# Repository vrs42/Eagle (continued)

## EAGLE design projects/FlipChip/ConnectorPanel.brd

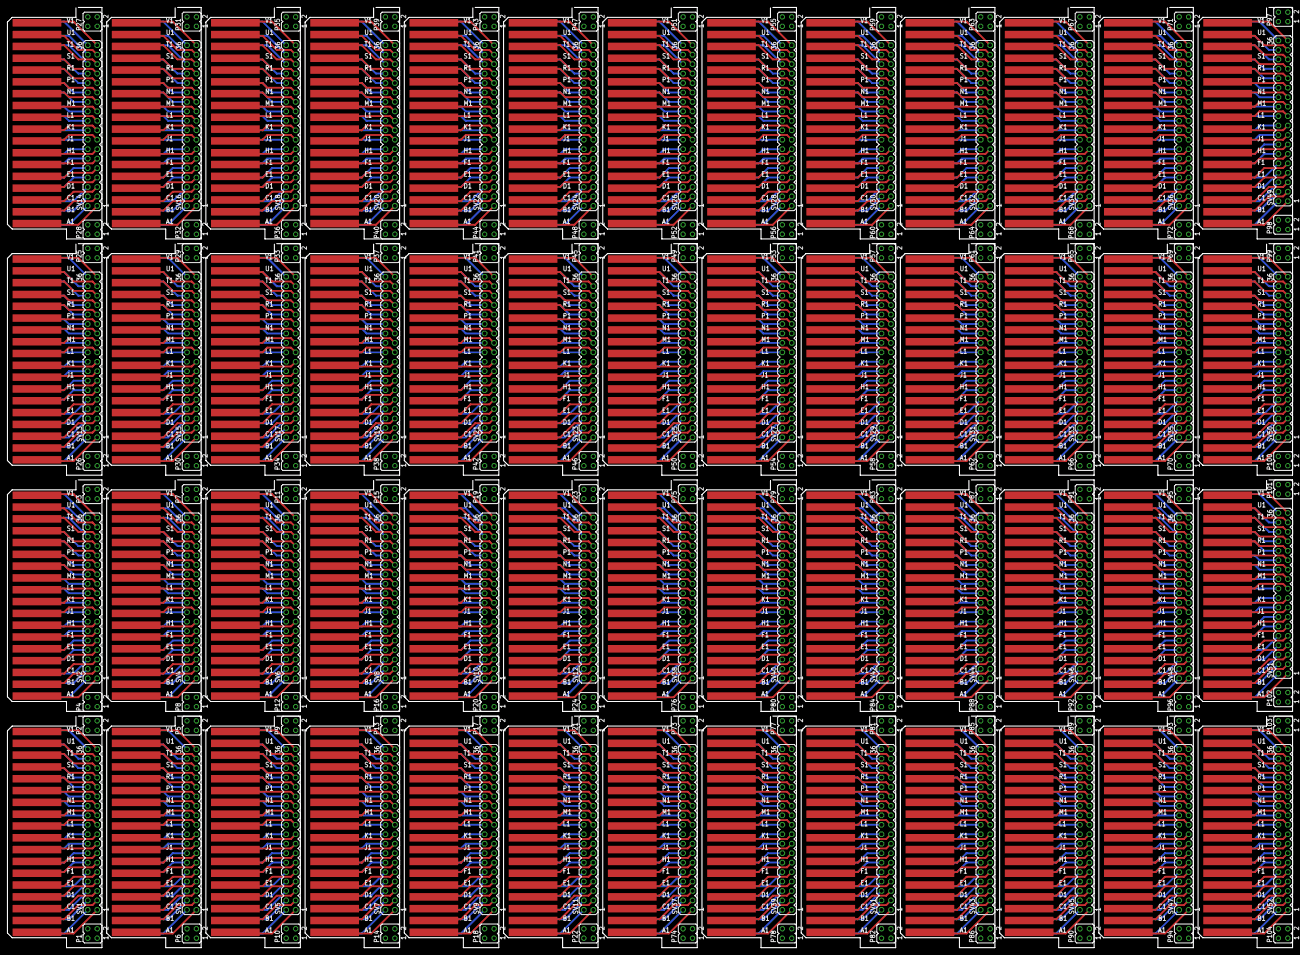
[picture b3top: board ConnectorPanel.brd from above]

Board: 2 copper layers, 345.4 x 252.7 mm, 208 parts (0 on the bottom side), 1872 nets.

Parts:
P1, P2, P3, P4, P5, P6, P7, P8, P9, P10, P11, P12, P13, P14, P15, P16, P17, P18, P19, P20, P21, P22, P23, P24, P25, P26, P27, P28, P29, P30, P31, P32, P33, P34, P35, P36, P37, P38, P39, P40, P41, P42, P43, P44, P45, P46, P47, P48, P49, P50, P51, P52, P53, P54, P55, P56, P57, P58, P59, P60, P61, P62, P63, P64, P65, P66, P67, P68, P69, P70, P71, P72, P73, P74, P75, P76, P77, P78, P79, P80, P81, P82, P83, P84, P85, P86, P87, P88, P89, P90, P91, P92, P93, P94, P95, P96, P97, P98, P99, P100, P101, P102, P103, P104: JP2Q
SV1, SV2, SV3, SV4, SV5, SV6, SV7, SV8, SV9, SV10, SV11, SV12, SV13, SV14, SV15, SV16, SV17, SV18, SV19, SV20, SV21, SV22, SV23, SV24, SV25, SV26, SV27, SV28, SV29, SV30, SV31, SV32, SV33, SV34, SV35, SV36, SV37, SV38, SV39, SV40, SV41, SV42, SV43, SV44, SV45, SV46, SV47, SV48, SV49, SV50, SV51, SV52: MA18-2
U$1, U$2, U$3, U$4, U$5, U$6, U$7, U$8, U$9, U$10, U$11, U$12, U$13, U$14, U$15, U$16, U$17, U$18, U$19, U$20, U$21, U$22, U$23, U$24, U$25, U$26, U$27, U$28, U$29, U$30, U$31, U$32, U$33, U$34, U$35, U$36, U$37, U$38, U$39, U$40, U$41, U$42, U$43, U$44, U$45, U$46, U$47, U$48, U$49, U$50, U$51, U$52: EDGE-CON2

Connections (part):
unnamed: SV1.36, U$1.V2
unnamed: SV1.34, U$1.U2
unnamed: SV1.32, U$1.T2
unnamed: SV1.30, U$1.S2
unnamed: SV1.28, U$1.R2
unnamed: SV1.26, U$1.P2
unnamed: SV1.24, U$1.N2
unnamed: SV1.22, U$1.M2
unnamed: SV1.20, U$1.L2
unnamed: SV1.18, U$1.K2
unnamed: SV1.16, U$1.J2
unnamed: SV1.14, U$1.H2
unnamed: SV1.12, U$1.F2
unnamed: SV1.10, U$1.E2
unnamed: SV1.8, U$1.D2
unnamed: SV1.6, U$1.C2
unnamed: SV1.4, U$1.B2
unnamed: SV1.2, U$1.A2
unnamed: SV1.35, U$1.V1
unnamed: SV1.33, U$1.U1
unnamed: SV1.31, U$1.T1
unnamed: SV1.29, U$1.S1
unnamed: SV1.27, U$1.R1
unnamed: SV1.25, U$1.P1
unnamed: SV1.23, U$1.N1
unnamed: SV1.21, U$1.M1
unnamed: SV1.19, U$1.L1
unnamed: SV1.17, U$1.K1
unnamed: SV1.15, U$1.J1
unnamed: SV1.13, U$1.H1
unnamed: SV1.11, U$1.F1
unnamed: SV1.9, U$1.E1
unnamed: SV1.7, U$1.D1
unnamed: SV1.5, U$1.C1
unnamed: SV1.3, U$1.B1
unnamed: SV1.1, U$1.A1
unnamed: SV2.36, U$2.V2
unnamed: SV2.34, U$2.U2
unnamed: SV2.32, U$2.T2
unnamed: SV2.30, U$2.S2
unnamed: SV2.28, U$2.R2
unnamed: SV2.26, U$2.P2
unnamed: SV2.24, U$2.N2
unnamed: SV2.22, U$2.M2
unnamed: SV2.20, U$2.L2
unnamed: SV2.18, U$2.K2
unnamed: SV2.16, U$2.J2
unnamed: SV2.14, U$2.H2
unnamed: SV2.12, U$2.F2
unnamed: SV2.10, U$2.E2
unnamed: SV2.8, U$2.D2
unnamed: SV2.6, U$2.C2
unnamed: SV2.4, U$2.B2
unnamed: SV2.2, U$2.A2
unnamed: SV2.35, U$2.V1
unnamed: SV2.33, U$2.U1
unnamed: SV2.31, U$2.T1
unnamed: SV2.29, U$2.S1
unnamed: SV2.27, U$2.R1
unnamed: SV2.25, U$2.P1
unnamed: SV2.23, U$2.N1
unnamed: SV2.21, U$2.M1
unnamed: SV2.19, U$2.L1
unnamed: SV2.17, U$2.K1
unnamed: SV2.15, U$2.J1
unnamed: SV2.13, U$2.H1
unnamed: SV2.11, U$2.F1
unnamed: SV2.9, U$2.E1
unnamed: SV2.7, U$2.D1
unnamed: SV2.5, U$2.C1
unnamed: SV2.3, U$2.B1
unnamed: SV2.1, U$2.A1
unnamed: SV3.36, U$3.V2
unnamed: SV3.34, U$3.U2
unnamed: SV3.32, U$3.T2
unnamed: SV3.30, U$3.S2
unnamed: SV3.28, U$3.R2
unnamed: SV3.26, U$3.P2
unnamed: SV3.24, U$3.N2
unnamed: SV3.22, U$3.M2
unnamed: SV3.20, U$3.L2
unnamed: SV3.18, U$3.K2
unnamed: SV3.16, U$3.J2
unnamed: SV3.14, U$3.H2
unnamed: SV3.12, U$3.F2
unnamed: SV3.10, U$3.E2
unnamed: SV3.8, U$3.D2
unnamed: SV3.6, U$3.C2
unnamed: SV3.4, U$3.B2
unnamed: SV3.2, U$3.A2
unnamed: SV3.35, U$3.V1
unnamed: SV3.33, U$3.U1
unnamed: SV3.31, U$3.T1
unnamed: SV3.29, U$3.S1
unnamed: SV3.27, U$3.R1
unnamed: SV3.25, U$3.P1
unnamed: SV3.23, U$3.N1
unnamed: SV3.21, U$3.M1
unnamed: SV3.19, U$3.L1
unnamed: SV3.17, U$3.K1
unnamed: SV3.15, U$3.J1
unnamed: SV3.13, U$3.H1
unnamed: SV3.11, U$3.F1
unnamed: SV3.9, U$3.E1
unnamed: SV3.7, U$3.D1
unnamed: SV3.5, U$3.C1
unnamed: SV3.3, U$3.B1
unnamed: SV3.1, U$3.A1
unnamed: SV4.36, U$4.V2
unnamed: SV4.34, U$4.U2
unnamed: SV4.32, U$4.T2
unnamed: SV4.30, U$4.S2
unnamed: SV4.28, U$4.R2
unnamed: SV4.26, U$4.P2
unnamed: SV4.24, U$4.N2
unnamed: SV4.22, U$4.M2
unnamed: SV4.20, U$4.L2
unnamed: SV4.18, U$4.K2
unnamed: SV4.16, U$4.J2
unnamed: SV4.14, U$4.H2
unnamed: SV4.12, U$4.F2
unnamed: SV4.10, U$4.E2
unnamed: SV4.8, U$4.D2
unnamed: SV4.6, U$4.C2
unnamed: SV4.4, U$4.B2
unnamed: SV4.2, U$4.A2
unnamed: SV4.35, U$4.V1
unnamed: SV4.33, U$4.U1
unnamed: SV4.31, U$4.T1
unnamed: SV4.29, U$4.S1
unnamed: SV4.27, U$4.R1
unnamed: SV4.25, U$4.P1
unnamed: SV4.23, U$4.N1
unnamed: SV4.21, U$4.M1
unnamed: SV4.19, U$4.L1
unnamed: SV4.17, U$4.K1
unnamed: SV4.15, U$4.J1
unnamed: SV4.13, U$4.H1
unnamed: SV4.11, U$4.F1
unnamed: SV4.9, U$4.E1
unnamed: SV4.7, U$4.D1
unnamed: SV4.5, U$4.C1
unnamed: SV4.3, U$4.B1
unnamed: SV4.1, U$4.A1
unnamed: SV5.36, U$5.V2
unnamed: SV5.34, U$5.U2
unnamed: SV5.32, U$5.T2
unnamed: SV5.30, U$5.S2
unnamed: SV5.28, U$5.R2
unnamed: SV5.26, U$5.P2
unnamed: SV5.24, U$5.N2
unnamed: SV5.22, U$5.M2
unnamed: SV5.20, U$5.L2
unnamed: SV5.18, U$5.K2
unnamed: SV5.16, U$5.J2
unnamed: SV5.14, U$5.H2
unnamed: SV5.12, U$5.F2
unnamed: SV5.10, U$5.E2
unnamed: SV5.8, U$5.D2
unnamed: SV5.6, U$5.C2
unnamed: SV5.4, U$5.B2
unnamed: SV5.2, U$5.A2
unnamed: SV5.35, U$5.V1
unnamed: SV5.33, U$5.U1
unnamed: SV5.31, U$5.T1
unnamed: SV5.29, U$5.S1
unnamed: SV5.27, U$5.R1
unnamed: SV5.25, U$5.P1
unnamed: SV5.23, U$5.N1
unnamed: SV5.21, U$5.M1
unnamed: SV5.19, U$5.L1
unnamed: SV5.17, U$5.K1
unnamed: SV5.15, U$5.J1
unnamed: SV5.13, U$5.H1
unnamed: SV5.11, U$5.F1
unnamed: SV5.9, U$5.E1
unnamed: SV5.7, U$5.D1
unnamed: SV5.5, U$5.C1
unnamed: SV5.3, U$5.B1
unnamed: SV5.1, U$5.A1
unnamed: SV6.36, U$6.V2
unnamed: SV6.34, U$6.U2
unnamed: SV6.32, U$6.T2
unnamed: SV6.30, U$6.S2
unnamed: SV6.28, U$6.R2
unnamed: SV6.26, U$6.P2
unnamed: SV6.24, U$6.N2
unnamed: SV6.22, U$6.M2
unnamed: SV6.20, U$6.L2
unnamed: SV6.18, U$6.K2
unnamed: SV6.16, U$6.J2
unnamed: SV6.14, U$6.H2
unnamed: SV6.12, U$6.F2
unnamed: SV6.10, U$6.E2
unnamed: SV6.8, U$6.D2
unnamed: SV6.6, U$6.C2
unnamed: SV6.4, U$6.B2
unnamed: SV6.2, U$6.A2
unnamed: SV6.35, U$6.V1
unnamed: SV6.33, U$6.U1
unnamed: SV6.31, U$6.T1
unnamed: SV6.29, U$6.S1
unnamed: SV6.27, U$6.R1
unnamed: SV6.25, U$6.P1
unnamed: SV6.23, U$6.N1
unnamed: SV6.21, U$6.M1
unnamed: SV6.19, U$6.L1
unnamed: SV6.17, U$6.K1
unnamed: SV6.15, U$6.J1
unnamed: SV6.13, U$6.H1
unnamed: SV6.11, U$6.F1
unnamed: SV6.9, U$6.E1
unnamed: SV6.7, U$6.D1
unnamed: SV6.5, U$6.C1
unnamed: SV6.3, U$6.B1
unnamed: SV6.1, U$6.A1
unnamed: SV7.36, U$7.V2
unnamed: SV7.34, U$7.U2
unnamed: SV7.32, U$7.T2
unnamed: SV7.30, U$7.S2
unnamed: SV7.28, U$7.R2
unnamed: SV7.26, U$7.P2
unnamed: SV7.24, U$7.N2
unnamed: SV7.22, U$7.M2
unnamed: SV7.20, U$7.L2
unnamed: SV7.18, U$7.K2
unnamed: SV7.16, U$7.J2
unnamed: SV7.14, U$7.H2
unnamed: SV7.12, U$7.F2
unnamed: SV7.10, U$7.E2
unnamed: SV7.8, U$7.D2
unnamed: SV7.6, U$7.C2
unnamed: SV7.4, U$7.B2
unnamed: SV7.2, U$7.A2
unnamed: SV7.35, U$7.V1
unnamed: SV7.33, U$7.U1
unnamed: SV7.31, U$7.T1
unnamed: SV7.29, U$7.S1
unnamed: SV7.27, U$7.R1
unnamed: SV7.25, U$7.P1
unnamed: SV7.23, U$7.N1
unnamed: SV7.21, U$7.M1
unnamed: SV7.19, U$7.L1
unnamed: SV7.17, U$7.K1
unnamed: SV7.15, U$7.J1
unnamed: SV7.13, U$7.H1
unnamed: SV7.11, U$7.F1
unnamed: SV7.9, U$7.E1
unnamed: SV7.7, U$7.D1
unnamed: SV7.5, U$7.C1
unnamed: SV7.3, U$7.B1
unnamed: SV7.1, U$7.A1
unnamed: SV8.36, U$8.V2
unnamed: SV8.34, U$8.U2
unnamed: SV8.32, U$8.T2
unnamed: SV8.30, U$8.S2
unnamed: SV8.28, U$8.R2
unnamed: SV8.26, U$8.P2
unnamed: SV8.24, U$8.N2
unnamed: SV8.22, U$8.M2
unnamed: SV8.20, U$8.L2
unnamed: SV8.18, U$8.K2
unnamed: SV8.16, U$8.J2
unnamed: SV8.14, U$8.H2
unnamed: SV8.12, U$8.F2
unnamed: SV8.10, U$8.E2
unnamed: SV8.8, U$8.D2
unnamed: SV8.6, U$8.C2
unnamed: SV8.4, U$8.B2
unnamed: SV8.2, U$8.A2
unnamed: SV8.35, U$8.V1
unnamed: SV8.33, U$8.U1
unnamed: SV8.31, U$8.T1
unnamed: SV8.29, U$8.S1
unnamed: SV8.27, U$8.R1
unnamed: SV8.25, U$8.P1
unnamed: SV8.23, U$8.N1
unnamed: SV8.21, U$8.M1
unnamed: SV8.19, U$8.L1
unnamed: SV8.17, U$8.K1
unnamed: SV8.15, U$8.J1
unnamed: SV8.13, U$8.H1
unnamed: SV8.11, U$8.F1
unnamed: SV8.9, U$8.E1
unnamed: SV8.7, U$8.D1
unnamed: SV8.5, U$8.C1
unnamed: SV8.3, U$8.B1
unnamed: SV8.1, U$8.A1
unnamed: SV9.36, U$9.V2
unnamed: SV9.34, U$9.U2
unnamed: SV9.32, U$9.T2
unnamed: SV9.30, U$9.S2
unnamed: SV9.28, U$9.R2
unnamed: SV9.26, U$9.P2
unnamed: SV9.24, U$9.N2
unnamed: SV9.22, U$9.M2
unnamed: SV9.20, U$9.L2
unnamed: SV9.18, U$9.K2
unnamed: SV9.16, U$9.J2
unnamed: SV9.14, U$9.H2
unnamed: SV9.12, U$9.F2
unnamed: SV9.10, U$9.E2
unnamed: SV9.8, U$9.D2
unnamed: SV9.6, U$9.C2
unnamed: SV9.4, U$9.B2
unnamed: SV9.2, U$9.A2
unnamed: SV9.35, U$9.V1
unnamed: SV9.33, U$9.U1
unnamed: SV9.31, U$9.T1
unnamed: SV9.29, U$9.S1
unnamed: SV9.27, U$9.R1
unnamed: SV9.25, U$9.P1
unnamed: SV9.23, U$9.N1
unnamed: SV9.21, U$9.M1
unnamed: SV9.19, U$9.L1
unnamed: SV9.17, U$9.K1
unnamed: SV9.15, U$9.J1
unnamed: SV9.13, U$9.H1
unnamed: SV9.11, U$9.F1
unnamed: SV9.9, U$9.E1
unnamed: SV9.7, U$9.D1
unnamed: SV9.5, U$9.C1
unnamed: SV9.3, U$9.B1
unnamed: SV9.1, U$9.A1
unnamed: SV10.36, U$10.V2
unnamed: SV10.34, U$10.U2
unnamed: SV10.32, U$10.T2
unnamed: SV10.30, U$10.S2
unnamed: SV10.28, U$10.R2
unnamed: SV10.26, U$10.P2
unnamed: SV10.24, U$10.N2
unnamed: SV10.22, U$10.M2
unnamed: SV10.20, U$10.L2
unnamed: SV10.18, U$10.K2
unnamed: SV10.16, U$10.J2
unnamed: SV10.14, U$10.H2
unnamed: SV10.12, U$10.F2
unnamed: SV10.10, U$10.E2
unnamed: SV10.8, U$10.D2
unnamed: SV10.6, U$10.C2
unnamed: SV10.4, U$10.B2
unnamed: SV10.2, U$10.A2
unnamed: SV10.35, U$10.V1
unnamed: SV10.33, U$10.U1
unnamed: SV10.31, U$10.T1
unnamed: SV10.29, U$10.S1
unnamed: SV10.27, U$10.R1
unnamed: SV10.25, U$10.P1
unnamed: SV10.23, U$10.N1
unnamed: SV10.21, U$10.M1
unnamed: SV10.19, U$10.L1
unnamed: SV10.17, U$10.K1
unnamed: SV10.15, U$10.J1
unnamed: SV10.13, U$10.H1
unnamed: SV10.11, U$10.F1
unnamed: SV10.9, U$10.E1
unnamed: SV10.7, U$10.D1
unnamed: SV10.5, U$10.C1
unnamed: SV10.3, U$10.B1
unnamed: SV10.1, U$10.A1
unnamed: SV11.36, U$11.V2
unnamed: SV11.34, U$11.U2
unnamed: SV11.32, U$11.T2
unnamed: SV11.30, U$11.S2
unnamed: SV11.28, U$11.R2
unnamed: SV11.26, U$11.P2
unnamed: SV11.24, U$11.N2
unnamed: SV11.22, U$11.M2
unnamed: SV11.20, U$11.L2
unnamed: SV11.18, U$11.K2
unnamed: SV11.16, U$11.J2
unnamed: SV11.14, U$11.H2
unnamed: SV11.12, U$11.F2
unnamed: SV11.10, U$11.E2
unnamed: SV11.8, U$11.D2
unnamed: SV11.6, U$11.C2
unnamed: SV11.4, U$11.B2
unnamed: SV11.2, U$11.A2
unnamed: SV11.35, U$11.V1
unnamed: SV11.33, U$11.U1
unnamed: SV11.31, U$11.T1
unnamed: SV11.29, U$11.S1
unnamed: SV11.27, U$11.R1
unnamed: SV11.25, U$11.P1
unnamed: SV11.23, U$11.N1
unnamed: SV11.21, U$11.M1
unnamed: SV11.19, U$11.L1
unnamed: SV11.17, U$11.K1
unnamed: SV11.15, U$11.J1
unnamed: SV11.13, U$11.H1
unnamed: SV11.11, U$11.F1
unnamed: SV11.9, U$11.E1
unnamed: SV11.7, U$11.D1
unnamed: SV11.5, U$11.C1
unnamed: SV11.3, U$11.B1
unnamed: SV11.1, U$11.A1
unnamed: SV12.36, U$12.V2
unnamed: SV12.34, U$12.U2
unnamed: SV12.32, U$12.T2
unnamed: SV12.30, U$12.S2
unnamed: SV12.28, U$12.R2
unnamed: SV12.26, U$12.P2
unnamed: SV12.24, U$12.N2
unnamed: SV12.22, U$12.M2
unnamed: SV12.20, U$12.L2
unnamed: SV12.18, U$12.K2
unnamed: SV12.16, U$12.J2
unnamed: SV12.14, U$12.H2
unnamed: SV12.12, U$12.F2
unnamed: SV12.10, U$12.E2
unnamed: SV12.8, U$12.D2
unnamed: SV12.6, U$12.C2
unnamed: SV12.4, U$12.B2
unnamed: SV12.2, U$12.A2
unnamed: SV12.35, U$12.V1
unnamed: SV12.33, U$12.U1
unnamed: SV12.31, U$12.T1
unnamed: SV12.29, U$12.S1
unnamed: SV12.27, U$12.R1
unnamed: SV12.25, U$12.P1
unnamed: SV12.23, U$12.N1
unnamed: SV12.21, U$12.M1
unnamed: SV12.19, U$12.L1
unnamed: SV12.17, U$12.K1
unnamed: SV12.15, U$12.J1
unnamed: SV12.13, U$12.H1
unnamed: SV12.11, U$12.F1
unnamed: SV12.9, U$12.E1
unnamed: SV12.7, U$12.D1
unnamed: SV12.5, U$12.C1
unnamed: SV12.3, U$12.B1
unnamed: SV12.1, U$12.A1
unnamed: SV13.36, U$13.V2
unnamed: SV13.34, U$13.U2
unnamed: SV13.32, U$13.T2
unnamed: SV13.30, U$13.S2
unnamed: SV13.28, U$13.R2
unnamed: SV13.26, U$13.P2
unnamed: SV13.24, U$13.N2
unnamed: SV13.22, U$13.M2
unnamed: SV13.20, U$13.L2
unnamed: SV13.18, U$13.K2
unnamed: SV13.16, U$13.J2
unnamed: SV13.14, U$13.H2
unnamed: SV13.12, U$13.F2
unnamed: SV13.10, U$13.E2
unnamed: SV13.8, U$13.D2
unnamed: SV13.6, U$13.C2
unnamed: SV13.4, U$13.B2
unnamed: SV13.2, U$13.A2
unnamed: SV13.35, U$13.V1
unnamed: SV13.33, U$13.U1
unnamed: SV13.31, U$13.T1
unnamed: SV13.29, U$13.S1
unnamed: SV13.27, U$13.R1
unnamed: SV13.25, U$13.P1
unnamed: SV13.23, U$13.N1
unnamed: SV13.21, U$13.M1
unnamed: SV13.19, U$13.L1
unnamed: SV13.17, U$13.K1
unnamed: SV13.15, U$13.J1
unnamed: SV13.13, U$13.H1
unnamed: SV13.11, U$13.F1
unnamed: SV13.9, U$13.E1
unnamed: SV13.7, U$13.D1
unnamed: SV13.5, U$13.C1
unnamed: SV13.3, U$13.B1
unnamed: SV13.1, U$13.A1
unnamed: SV14.36, U$14.V2
unnamed: SV14.34, U$14.U2
unnamed: SV14.32, U$14.T2
unnamed: SV14.30, U$14.S2
unnamed: SV14.28, U$14.R2
unnamed: SV14.26, U$14.P2
unnamed: SV14.24, U$14.N2
unnamed: SV14.22, U$14.M2
unnamed: SV14.20, U$14.L2
unnamed: SV14.18, U$14.K2
unnamed: SV14.16, U$14.J2
unnamed: SV14.14, U$14.H2
unnamed: SV14.12, U$14.F2
unnamed: SV14.10, U$14.E2
unnamed: SV14.8, U$14.D2
unnamed: SV14.6, U$14.C2
unnamed: SV14.4, U$14.B2
unnamed: SV14.2, U$14.A2
unnamed: SV14.35, U$14.V1
unnamed: SV14.33, U$14.U1
unnamed: SV14.31, U$14.T1
unnamed: SV14.29, U$14.S1
unnamed: SV14.27, U$14.R1
unnamed: SV14.25, U$14.P1
unnamed: SV14.23, U$14.N1
unnamed: SV14.21, U$14.M1
unnamed: SV14.19, U$14.L1
unnamed: SV14.17, U$14.K1
unnamed: SV14.15, U$14.J1
unnamed: SV14.13, U$14.H1
unnamed: SV14.11, U$14.F1
unnamed: SV14.9, U$14.E1
unnamed: SV14.7, U$14.D1
unnamed: SV14.5, U$14.C1
unnamed: SV14.3, U$14.B1
unnamed: SV14.1, U$14.A1
unnamed: SV15.36, U$15.V2
unnamed: SV15.34, U$15.U2
unnamed: SV15.32, U$15.T2
unnamed: SV15.30, U$15.S2
unnamed: SV15.28, U$15.R2
unnamed: SV15.26, U$15.P2
unnamed: SV15.24, U$15.N2
unnamed: SV15.22, U$15.M2
unnamed: SV15.20, U$15.L2
unnamed: SV15.18, U$15.K2
unnamed: SV15.16, U$15.J2
unnamed: SV15.14, U$15.H2
unnamed: SV15.12, U$15.F2
unnamed: SV15.10, U$15.E2
unnamed: SV15.8, U$15.D2
unnamed: SV15.6, U$15.C2
unnamed: SV15.4, U$15.B2
unnamed: SV15.2, U$15.A2
unnamed: SV15.35, U$15.V1
unnamed: SV15.33, U$15.U1
unnamed: SV15.31, U$15.T1
unnamed: SV15.29, U$15.S1
unnamed: SV15.27, U$15.R1
unnamed: SV15.25, U$15.P1
unnamed: SV15.23, U$15.N1
unnamed: SV15.21, U$15.M1
unnamed: SV15.19, U$15.L1
unnamed: SV15.17, U$15.K1
unnamed: SV15.15, U$15.J1
unnamed: SV15.13, U$15.H1
unnamed: SV15.11, U$15.F1
unnamed: SV15.9, U$15.E1
unnamed: SV15.7, U$15.D1
unnamed: SV15.5, U$15.C1
unnamed: SV15.3, U$15.B1
unnamed: SV15.1, U$15.A1
unnamed: SV16.36, U$16.V2
unnamed: SV16.34, U$16.U2
unnamed: SV16.32, U$16.T2
unnamed: SV16.30, U$16.S2
unnamed: SV16.28, U$16.R2
unnamed: SV16.26, U$16.P2
unnamed: SV16.24, U$16.N2
unnamed: SV16.22, U$16.M2
unnamed: SV16.20, U$16.L2
unnamed: SV16.18, U$16.K2
unnamed: SV16.16, U$16.J2
unnamed: SV16.14, U$16.H2
unnamed: SV16.12, U$16.F2
unnamed: SV16.10, U$16.E2
unnamed: SV16.8, U$16.D2
unnamed: SV16.6, U$16.C2
unnamed: SV16.4, U$16.B2
unnamed: SV16.2, U$16.A2
unnamed: SV16.35, U$16.V1
unnamed: SV16.33, U$16.U1
unnamed: SV16.31, U$16.T1
unnamed: SV16.29, U$16.S1
unnamed: SV16.27, U$16.R1
unnamed: SV16.25, U$16.P1
unnamed: SV16.23, U$16.N1
unnamed: SV16.21, U$16.M1
unnamed: SV16.19, U$16.L1
unnamed: SV16.17, U$16.K1
unnamed: SV16.15, U$16.J1
unnamed: SV16.13, U$16.H1
unnamed: SV16.11, U$16.F1
unnamed: SV16.9, U$16.E1
unnamed: SV16.7, U$16.D1
unnamed: SV16.5, U$16.C1
unnamed: SV16.3, U$16.B1
unnamed: SV16.1, U$16.A1
unnamed: SV17.36, U$17.V2
unnamed: SV17.34, U$17.U2
unnamed: SV17.32, U$17.T2
unnamed: SV17.30, U$17.S2
unnamed: SV17.28, U$17.R2
unnamed: SV17.26, U$17.P2
unnamed: SV17.24, U$17.N2
unnamed: SV17.22, U$17.M2
unnamed: SV17.20, U$17.L2
unnamed: SV17.18, U$17.K2
unnamed: SV17.16, U$17.J2
unnamed: SV17.14, U$17.H2
unnamed: SV17.12, U$17.F2
unnamed: SV17.10, U$17.E2
unnamed: SV17.8, U$17.D2
unnamed: SV17.6, U$17.C2
unnamed: SV17.4, U$17.B2
unnamed: SV17.2, U$17.A2
unnamed: SV17.35, U$17.V1
unnamed: SV17.33, U$17.U1
unnamed: SV17.31, U$17.T1
unnamed: SV17.29, U$17.S1
unnamed: SV17.27, U$17.R1
unnamed: SV17.25, U$17.P1
unnamed: SV17.23, U$17.N1
unnamed: SV17.21, U$17.M1
unnamed: SV17.19, U$17.L1
unnamed: SV17.17, U$17.K1
unnamed: SV17.15, U$17.J1
unnamed: SV17.13, U$17.H1
unnamed: SV17.11, U$17.F1
unnamed: SV17.9, U$17.E1
unnamed: SV17.7, U$17.D1
unnamed: SV17.5, U$17.C1
unnamed: SV17.3, U$17.B1
unnamed: SV17.1, U$17.A1
unnamed: SV18.36, U$18.V2
unnamed: SV18.34, U$18.U2
unnamed: SV18.32, U$18.T2
unnamed: SV18.30, U$18.S2
unnamed: SV18.28, U$18.R2
unnamed: SV18.26, U$18.P2
unnamed: SV18.24, U$18.N2
unnamed: SV18.22, U$18.M2
unnamed: SV18.20, U$18.L2
unnamed: SV18.18, U$18.K2
unnamed: SV18.16, U$18.J2
unnamed: SV18.14, U$18.H2
unnamed: SV18.12, U$18.F2
unnamed: SV18.10, U$18.E2
unnamed: SV18.8, U$18.D2
unnamed: SV18.6, U$18.C2
unnamed: SV18.4, U$18.B2
unnamed: SV18.2, U$18.A2
unnamed: SV18.35, U$18.V1
unnamed: SV18.33, U$18.U1
unnamed: SV18.31, U$18.T1
unnamed: SV18.29, U$18.S1
unnamed: SV18.27, U$18.R1
unnamed: SV18.25, U$18.P1
unnamed: SV18.23, U$18.N1
unnamed: SV18.21, U$18.M1
unnamed: SV18.19, U$18.L1
unnamed: SV18.17, U$18.K1
unnamed: SV18.15, U$18.J1
unnamed: SV18.13, U$18.H1
unnamed: SV18.11, U$18.F1
unnamed: SV18.9, U$18.E1
unnamed: SV18.7, U$18.D1
unnamed: SV18.5, U$18.C1
unnamed: SV18.3, U$18.B1
unnamed: SV18.1, U$18.A1
unnamed: SV19.36, U$19.V2
unnamed: SV19.34, U$19.U2
unnamed: SV19.32, U$19.T2
unnamed: SV19.30, U$19.S2
unnamed: SV19.28, U$19.R2
unnamed: SV19.26, U$19.P2
unnamed: SV19.24, U$19.N2
unnamed: SV19.22, U$19.M2
unnamed: SV19.20, U$19.L2
unnamed: SV19.18, U$19.K2
unnamed: SV19.16, U$19.J2
unnamed: SV19.14, U$19.H2
unnamed: SV19.12, U$19.F2
unnamed: SV19.10, U$19.E2
unnamed: SV19.8, U$19.D2
unnamed: SV19.6, U$19.C2
unnamed: SV19.4, U$19.B2
unnamed: SV19.2, U$19.A2
unnamed: SV19.35, U$19.V1
unnamed: SV19.33, U$19.U1
unnamed: SV19.31, U$19.T1
unnamed: SV19.29, U$19.S1
unnamed: SV19.27, U$19.R1
unnamed: SV19.25, U$19.P1
unnamed: SV19.23, U$19.N1
unnamed: SV19.21, U$19.M1
unnamed: SV19.19, U$19.L1
unnamed: SV19.17, U$19.K1
unnamed: SV19.15, U$19.J1
unnamed: SV19.13, U$19.H1
unnamed: SV19.11, U$19.F1
unnamed: SV19.9, U$19.E1
unnamed: SV19.7, U$19.D1
unnamed: SV19.5, U$19.C1
unnamed: SV19.3, U$19.B1
unnamed: SV19.1, U$19.A1
unnamed: SV20.36, U$20.V2
unnamed: SV20.34, U$20.U2
unnamed: SV20.32, U$20.T2
unnamed: SV20.30, U$20.S2
unnamed: SV20.28, U$20.R2
unnamed: SV20.26, U$20.P2
unnamed: SV20.24, U$20.N2
unnamed: SV20.22, U$20.M2
unnamed: SV20.20, U$20.L2
unnamed: SV20.18, U$20.K2
unnamed: SV20.16, U$20.J2
unnamed: SV20.14, U$20.H2
unnamed: SV20.12, U$20.F2
unnamed: SV20.10, U$20.E2
unnamed: SV20.8, U$20.D2
unnamed: SV20.6, U$20.C2
unnamed: SV20.4, U$20.B2
unnamed: SV20.2, U$20.A2
unnamed: SV20.35, U$20.V1
unnamed: SV20.33, U$20.U1
unnamed: SV20.31, U$20.T1
unnamed: SV20.29, U$20.S1
unnamed: SV20.27, U$20.R1
unnamed: SV20.25, U$20.P1
unnamed: SV20.23, U$20.N1
unnamed: SV20.21, U$20.M1
unnamed: SV20.19, U$20.L1
unnamed: SV20.17, U$20.K1
unnamed: SV20.15, U$20.J1
unnamed: SV20.13, U$20.H1
unnamed: SV20.11, U$20.F1
unnamed: SV20.9, U$20.E1
unnamed: SV20.7, U$20.D1
unnamed: SV20.5, U$20.C1
unnamed: SV20.3, U$20.B1
unnamed: SV20.1, U$20.A1
unnamed: SV21.36, U$21.V2
unnamed: SV21.34, U$21.U2
unnamed: SV21.32, U$21.T2
unnamed: SV21.30, U$21.S2
unnamed: SV21.28, U$21.R2
unnamed: SV21.26, U$21.P2
unnamed: SV21.24, U$21.N2
unnamed: SV21.22, U$21.M2
unnamed: SV21.20, U$21.L2
unnamed: SV21.18, U$21.K2
unnamed: SV21.16, U$21.J2
unnamed: SV21.14, U$21.H2
unnamed: SV21.12, U$21.F2
unnamed: SV21.10, U$21.E2
unnamed: SV21.8, U$21.D2
unnamed: SV21.6, U$21.C2
unnamed: SV21.4, U$21.B2
unnamed: SV21.2, U$21.A2
unnamed: SV21.35, U$21.V1
unnamed: SV21.33, U$21.U1
unnamed: SV21.31, U$21.T1
unnamed: SV21.29, U$21.S1
unnamed: SV21.27, U$21.R1
unnamed: SV21.25, U$21.P1
unnamed: SV21.23, U$21.N1
unnamed: SV21.21, U$21.M1
unnamed: SV21.19, U$21.L1
unnamed: SV21.17, U$21.K1
unnamed: SV21.15, U$21.J1
unnamed: SV21.13, U$21.H1
unnamed: SV21.11, U$21.F1
unnamed: SV21.9, U$21.E1
unnamed: SV21.7, U$21.D1
unnamed: SV21.5, U$21.C1
unnamed: SV21.3, U$21.B1
unnamed: SV21.1, U$21.A1
unnamed: SV22.36, U$22.V2
unnamed: SV22.34, U$22.U2
unnamed: SV22.32, U$22.T2
unnamed: SV22.30, U$22.S2
unnamed: SV22.28, U$22.R2
unnamed: SV22.26, U$22.P2
unnamed: SV22.24, U$22.N2
unnamed: SV22.22, U$22.M2
unnamed: SV22.20, U$22.L2
unnamed: SV22.18, U$22.K2
unnamed: SV22.16, U$22.J2
unnamed: SV22.14, U$22.H2
unnamed: SV22.12, U$22.F2
unnamed: SV22.10, U$22.E2
unnamed: SV22.8, U$22.D2
unnamed: SV22.6, U$22.C2
unnamed: SV22.4, U$22.B2
unnamed: SV22.2, U$22.A2
unnamed: SV22.35, U$22.V1
unnamed: SV22.33, U$22.U1
unnamed: SV22.31, U$22.T1
unnamed: SV22.29, U$22.S1
unnamed: SV22.27, U$22.R1
unnamed: SV22.25, U$22.P1
unnamed: SV22.23, U$22.N1
unnamed: SV22.21, U$22.M1
unnamed: SV22.19, U$22.L1
unnamed: SV22.17, U$22.K1
unnamed: SV22.15, U$22.J1
unnamed: SV22.13, U$22.H1
unnamed: SV22.11, U$22.F1
unnamed: SV22.9, U$22.E1
unnamed: SV22.7, U$22.D1
unnamed: SV22.5, U$22.C1
unnamed: SV22.3, U$22.B1
unnamed: SV22.1, U$22.A1
unnamed: SV23.36, U$23.V2
unnamed: SV23.34, U$23.U2
unnamed: SV23.32, U$23.T2
unnamed: SV23.30, U$23.S2
unnamed: SV23.28, U$23.R2
unnamed: SV23.26, U$23.P2
unnamed: SV23.24, U$23.N2
unnamed: SV23.22, U$23.M2
unnamed: SV23.20, U$23.L2
unnamed: SV23.18, U$23.K2
unnamed: SV23.16, U$23.J2
unnamed: SV23.14, U$23.H2
unnamed: SV23.12, U$23.F2
unnamed: SV23.10, U$23.E2
unnamed: SV23.8, U$23.D2
unnamed: SV23.6, U$23.C2
unnamed: SV23.4, U$23.B2
unnamed: SV23.2, U$23.A2
unnamed: SV23.35, U$23.V1
unnamed: SV23.33, U$23.U1
unnamed: SV23.31, U$23.T1
unnamed: SV23.29, U$23.S1
unnamed: SV23.27, U$23.R1
unnamed: SV23.25, U$23.P1
unnamed: SV23.23, U$23.N1
unnamed: SV23.21, U$23.M1
unnamed: SV23.19, U$23.L1
unnamed: SV23.17, U$23.K1
unnamed: SV23.15, U$23.J1
unnamed: SV23.13, U$23.H1
unnamed: SV23.11, U$23.F1
unnamed: SV23.9, U$23.E1
unnamed: SV23.7, U$23.D1
unnamed: SV23.5, U$23.C1
unnamed: SV23.3, U$23.B1
unnamed: SV23.1, U$23.A1
unnamed: SV24.36, U$24.V2
unnamed: SV24.34, U$24.U2
unnamed: SV24.32, U$24.T2
unnamed: SV24.30, U$24.S2
unnamed: SV24.28, U$24.R2
unnamed: SV24.26, U$24.P2
unnamed: SV24.24, U$24.N2
unnamed: SV24.22, U$24.M2
unnamed: SV24.20, U$24.L2
unnamed: SV24.18, U$24.K2
unnamed: SV24.16, U$24.J2
unnamed: SV24.14, U$24.H2
unnamed: SV24.12, U$24.F2
unnamed: SV24.10, U$24.E2
unnamed: SV24.8, U$24.D2
unnamed: SV24.6, U$24.C2
unnamed: SV24.4, U$24.B2
unnamed: SV24.2, U$24.A2
unnamed: SV24.35, U$24.V1
unnamed: SV24.33, U$24.U1
unnamed: SV24.31, U$24.T1
unnamed: SV24.29, U$24.S1
unnamed: SV24.27, U$24.R1
unnamed: SV24.25, U$24.P1
unnamed: SV24.23, U$24.N1
unnamed: SV24.21, U$24.M1
unnamed: SV24.19, U$24.L1
unnamed: SV24.17, U$24.K1
unnamed: SV24.15, U$24.J1
unnamed: SV24.13, U$24.H1
unnamed: SV24.11, U$24.F1
unnamed: SV24.9, U$24.E1
unnamed: SV24.7, U$24.D1
unnamed: SV24.5, U$24.C1
unnamed: SV24.3, U$24.B1
unnamed: SV24.1, U$24.A1
unnamed: SV25.36, U$25.V2
unnamed: SV25.34, U$25.U2
unnamed: SV25.32, U$25.T2
unnamed: SV25.30, U$25.S2
unnamed: SV25.28, U$25.R2
unnamed: SV25.26, U$25.P2
unnamed: SV25.24, U$25.N2
unnamed: SV25.22, U$25.M2
unnamed: SV25.20, U$25.L2
unnamed: SV25.18, U$25.K2
unnamed: SV25.16, U$25.J2
unnamed: SV25.14, U$25.H2
unnamed: SV25.12, U$25.F2
unnamed: SV25.10, U$25.E2
unnamed: SV25.8, U$25.D2
unnamed: SV25.6, U$25.C2
unnamed: SV25.4, U$25.B2
unnamed: SV25.2, U$25.A2
unnamed: SV25.35, U$25.V1
unnamed: SV25.33, U$25.U1
unnamed: SV25.31, U$25.T1
unnamed: SV25.29, U$25.S1
unnamed: SV25.27, U$25.R1
unnamed: SV25.25, U$25.P1
unnamed: SV25.23, U$25.N1
unnamed: SV25.21, U$25.M1
unnamed: SV25.19, U$25.L1
unnamed: SV25.17, U$25.K1
unnamed: SV25.15, U$25.J1
unnamed: SV25.13, U$25.H1
unnamed: SV25.11, U$25.F1
unnamed: SV25.9, U$25.E1
unnamed: SV25.7, U$25.D1
unnamed: SV25.5, U$25.C1
unnamed: SV25.3, U$25.B1
unnamed: SV25.1, U$25.A1
unnamed: SV26.36, U$26.V2
unnamed: SV26.34, U$26.U2
unnamed: SV26.32, U$26.T2
unnamed: SV26.30, U$26.S2
unnamed: SV26.28, U$26.R2
unnamed: SV26.26, U$26.P2
unnamed: SV26.24, U$26.N2
unnamed: SV26.22, U$26.M2
unnamed: SV26.20, U$26.L2
unnamed: SV26.18, U$26.K2
unnamed: SV26.16, U$26.J2
unnamed: SV26.14, U$26.H2
unnamed: SV26.12, U$26.F2
unnamed: SV26.10, U$26.E2
unnamed: SV26.8, U$26.D2
unnamed: SV26.6, U$26.C2
unnamed: SV26.4, U$26.B2
unnamed: SV26.2, U$26.A2
unnamed: SV26.35, U$26.V1
unnamed: SV26.33, U$26.U1
unnamed: SV26.31, U$26.T1
unnamed: SV26.29, U$26.S1
unnamed: SV26.27, U$26.R1
unnamed: SV26.25, U$26.P1
unnamed: SV26.23, U$26.N1
unnamed: SV26.21, U$26.M1
unnamed: SV26.19, U$26.L1
unnamed: SV26.17, U$26.K1
unnamed: SV26.15, U$26.J1
unnamed: SV26.13, U$26.H1
unnamed: SV26.11, U$26.F1
unnamed: SV26.9, U$26.E1
unnamed: SV26.7, U$26.D1
unnamed: SV26.5, U$26.C1
unnamed: SV26.3, U$26.B1
unnamed: SV26.1, U$26.A1
unnamed: SV27.36, U$27.V2
unnamed: SV27.34, U$27.U2
unnamed: SV27.32, U$27.T2
unnamed: SV27.30, U$27.S2
unnamed: SV27.28, U$27.R2
unnamed: SV27.26, U$27.P2
unnamed: SV27.24, U$27.N2
unnamed: SV27.22, U$27.M2
unnamed: SV27.20, U$27.L2
unnamed: SV27.18, U$27.K2
unnamed: SV27.16, U$27.J2
unnamed: SV27.14, U$27.H2
unnamed: SV27.12, U$27.F2
unnamed: SV27.10, U$27.E2
unnamed: SV27.8, U$27.D2
unnamed: SV27.6, U$27.C2
unnamed: SV27.4, U$27.B2
unnamed: SV27.2, U$27.A2
unnamed: SV27.35, U$27.V1
unnamed: SV27.33, U$27.U1
unnamed: SV27.31, U$27.T1
unnamed: SV27.29, U$27.S1
unnamed: SV27.27, U$27.R1
unnamed: SV27.25, U$27.P1
unnamed: SV27.23, U$27.N1
unnamed: SV27.21, U$27.M1
unnamed: SV27.19, U$27.L1
unnamed: SV27.17, U$27.K1
unnamed: SV27.15, U$27.J1
unnamed: SV27.13, U$27.H1
unnamed: SV27.11, U$27.F1
unnamed: SV27.9, U$27.E1
unnamed: SV27.7, U$27.D1
unnamed: SV27.5, U$27.C1
unnamed: SV27.3, U$27.B1
unnamed: SV27.1, U$27.A1
unnamed: SV28.36, U$28.V2
unnamed: SV28.34, U$28.U2
unnamed: SV28.32, U$28.T2
unnamed: SV28.30, U$28.S2
unnamed: SV28.28, U$28.R2
unnamed: SV28.26, U$28.P2
unnamed: SV28.24, U$28.N2
unnamed: SV28.22, U$28.M2
unnamed: SV28.20, U$28.L2
unnamed: SV28.18, U$28.K2
unnamed: SV28.16, U$28.J2
unnamed: SV28.14, U$28.H2
unnamed: SV28.12, U$28.F2
unnamed: SV28.10, U$28.E2
unnamed: SV28.8, U$28.D2
unnamed: SV28.6, U$28.C2
unnamed: SV28.4, U$28.B2
unnamed: SV28.2, U$28.A2
unnamed: SV28.35, U$28.V1
unnamed: SV28.33, U$28.U1
unnamed: SV28.31, U$28.T1
unnamed: SV28.29, U$28.S1
unnamed: SV28.27, U$28.R1
unnamed: SV28.25, U$28.P1
unnamed: SV28.23, U$28.N1
unnamed: SV28.21, U$28.M1
unnamed: SV28.19, U$28.L1
unnamed: SV28.17, U$28.K1
unnamed: SV28.15, U$28.J1
unnamed: SV28.13, U$28.H1
unnamed: SV28.11, U$28.F1
unnamed: SV28.9, U$28.E1
unnamed: SV28.7, U$28.D1
unnamed: SV28.5, U$28.C1
unnamed: SV28.3, U$28.B1
unnamed: SV28.1, U$28.A1
unnamed: SV29.36, U$29.V2
unnamed: SV29.34, U$29.U2
unnamed: SV29.32, U$29.T2
unnamed: SV29.30, U$29.S2
unnamed: SV29.28, U$29.R2
unnamed: SV29.26, U$29.P2
unnamed: SV29.24, U$29.N2
unnamed: SV29.22, U$29.M2
unnamed: SV29.20, U$29.L2
unnamed: SV29.18, U$29.K2
unnamed: SV29.16, U$29.J2
unnamed: SV29.14, U$29.H2
unnamed: SV29.12, U$29.F2
unnamed: SV29.10, U$29.E2
unnamed: SV29.8, U$29.D2
unnamed: SV29.6, U$29.C2
unnamed: SV29.4, U$29.B2
unnamed: SV29.2, U$29.A2
unnamed: SV29.35, U$29.V1
unnamed: SV29.33, U$29.U1
unnamed: SV29.31, U$29.T1
unnamed: SV29.29, U$29.S1
unnamed: SV29.27, U$29.R1
unnamed: SV29.25, U$29.P1
unnamed: SV29.23, U$29.N1
unnamed: SV29.21, U$29.M1
unnamed: SV29.19, U$29.L1
unnamed: SV29.17, U$29.K1
unnamed: SV29.15, U$29.J1
unnamed: SV29.13, U$29.H1
unnamed: SV29.11, U$29.F1
unnamed: SV29.9, U$29.E1
unnamed: SV29.7, U$29.D1
unnamed: SV29.5, U$29.C1
unnamed: SV29.3, U$29.B1
unnamed: SV29.1, U$29.A1
unnamed: SV30.36, U$30.V2
unnamed: SV30.34, U$30.U2
unnamed: SV30.32, U$30.T2
unnamed: SV30.30, U$30.S2
unnamed: SV30.28, U$30.R2
unnamed: SV30.26, U$30.P2
unnamed: SV30.24, U$30.N2
unnamed: SV30.22, U$30.M2
unnamed: SV30.20, U$30.L2
unnamed: SV30.18, U$30.K2
unnamed: SV30.16, U$30.J2
unnamed: SV30.14, U$30.H2
unnamed: SV30.12, U$30.F2
unnamed: SV30.10, U$30.E2
unnamed: SV30.8, U$30.D2
unnamed: SV30.6, U$30.C2
unnamed: SV30.4, U$30.B2
unnamed: SV30.2, U$30.A2
unnamed: SV30.35, U$30.V1
unnamed: SV30.33, U$30.U1
unnamed: SV30.31, U$30.T1
unnamed: SV30.29, U$30.S1
unnamed: SV30.27, U$30.R1
unnamed: SV30.25, U$30.P1
unnamed: SV30.23, U$30.N1
unnamed: SV30.21, U$30.M1
unnamed: SV30.19, U$30.L1
unnamed: SV30.17, U$30.K1
unnamed: SV30.15, U$30.J1
unnamed: SV30.13, U$30.H1
unnamed: SV30.11, U$30.F1
unnamed: SV30.9, U$30.E1
unnamed: SV30.7, U$30.D1
unnamed: SV30.5, U$30.C1
unnamed: SV30.3, U$30.B1
unnamed: SV30.1, U$30.A1
unnamed: SV31.36, U$31.V2
unnamed: SV31.34, U$31.U2
unnamed: SV31.32, U$31.T2
unnamed: SV31.30, U$31.S2
unnamed: SV31.28, U$31.R2
unnamed: SV31.26, U$31.P2
unnamed: SV31.24, U$31.N2
unnamed: SV31.22, U$31.M2
unnamed: SV31.20, U$31.L2
unnamed: SV31.18, U$31.K2
unnamed: SV31.16, U$31.J2
unnamed: SV31.14, U$31.H2
unnamed: SV31.12, U$31.F2
unnamed: SV31.10, U$31.E2
unnamed: SV31.8, U$31.D2
unnamed: SV31.6, U$31.C2
unnamed: SV31.4, U$31.B2
unnamed: SV31.2, U$31.A2
unnamed: SV31.35, U$31.V1
unnamed: SV31.33, U$31.U1
unnamed: SV31.31, U$31.T1
unnamed: SV31.29, U$31.S1
unnamed: SV31.27, U$31.R1
unnamed: SV31.25, U$31.P1
unnamed: SV31.23, U$31.N1
unnamed: SV31.21, U$31.M1
unnamed: SV31.19, U$31.L1
unnamed: SV31.17, U$31.K1
unnamed: SV31.15, U$31.J1
unnamed: SV31.13, U$31.H1
unnamed: SV31.11, U$31.F1
unnamed: SV31.9, U$31.E1
unnamed: SV31.7, U$31.D1
unnamed: SV31.5, U$31.C1
unnamed: SV31.3, U$31.B1
unnamed: SV31.1, U$31.A1
unnamed: SV32.36, U$32.V2
unnamed: SV32.34, U$32.U2
unnamed: SV32.32, U$32.T2
unnamed: SV32.30, U$32.S2
unnamed: SV32.28, U$32.R2
unnamed: SV32.26, U$32.P2
unnamed: SV32.24, U$32.N2
unnamed: SV32.22, U$32.M2
unnamed: SV32.20, U$32.L2
unnamed: SV32.18, U$32.K2
unnamed: SV32.16, U$32.J2
unnamed: SV32.14, U$32.H2
unnamed: SV32.12, U$32.F2
unnamed: SV32.10, U$32.E2
unnamed: SV32.8, U$32.D2
unnamed: SV32.6, U$32.C2
unnamed: SV32.4, U$32.B2
unnamed: SV32.2, U$32.A2
unnamed: SV32.35, U$32.V1
unnamed: SV32.33, U$32.U1
unnamed: SV32.31, U$32.T1
unnamed: SV32.29, U$32.S1
unnamed: SV32.27, U$32.R1
unnamed: SV32.25, U$32.P1
unnamed: SV32.23, U$32.N1
unnamed: SV32.21, U$32.M1
unnamed: SV32.19, U$32.L1
unnamed: SV32.17, U$32.K1
unnamed: SV32.15, U$32.J1
unnamed: SV32.13, U$32.H1
unnamed: SV32.11, U$32.F1
unnamed: SV32.9, U$32.E1
unnamed: SV32.7, U$32.D1
unnamed: SV32.5, U$32.C1
unnamed: SV32.3, U$32.B1
unnamed: SV32.1, U$32.A1
unnamed: SV33.36, U$33.V2
unnamed: SV33.34, U$33.U2
unnamed: SV33.32, U$33.T2
unnamed: SV33.30, U$33.S2
unnamed: SV33.28, U$33.R2
unnamed: SV33.26, U$33.P2
unnamed: SV33.24, U$33.N2
unnamed: SV33.22, U$33.M2
unnamed: SV33.20, U$33.L2
unnamed: SV33.18, U$33.K2
unnamed: SV33.16, U$33.J2
unnamed: SV33.14, U$33.H2
unnamed: SV33.12, U$33.F2
unnamed: SV33.10, U$33.E2
unnamed: SV33.8, U$33.D2
unnamed: SV33.6, U$33.C2
unnamed: SV33.4, U$33.B2
unnamed: SV33.2, U$33.A2
unnamed: SV33.35, U$33.V1
unnamed: SV33.33, U$33.U1
unnamed: SV33.31, U$33.T1
unnamed: SV33.29, U$33.S1
unnamed: SV33.27, U$33.R1
unnamed: SV33.25, U$33.P1
unnamed: SV33.23, U$33.N1
unnamed: SV33.21, U$33.M1
unnamed: SV33.19, U$33.L1
unnamed: SV33.17, U$33.K1
unnamed: SV33.15, U$33.J1
unnamed: SV33.13, U$33.H1
unnamed: SV33.11, U$33.F1
unnamed: SV33.9, U$33.E1
unnamed: SV33.7, U$33.D1
unnamed: SV33.5, U$33.C1
unnamed: SV33.3, U$33.B1
unnamed: SV33.1, U$33.A1
unnamed: SV34.36, U$34.V2
unnamed: SV34.34, U$34.U2
unnamed: SV34.32, U$34.T2
unnamed: SV34.30, U$34.S2
unnamed: SV34.28, U$34.R2
unnamed: SV34.26, U$34.P2
unnamed: SV34.24, U$34.N2
unnamed: SV34.22, U$34.M2
unnamed: SV34.20, U$34.L2
unnamed: SV34.18, U$34.K2
unnamed: SV34.16, U$34.J2
unnamed: SV34.14, U$34.H2
unnamed: SV34.12, U$34.F2
unnamed: SV34.10, U$34.E2
unnamed: SV34.8, U$34.D2
unnamed: SV34.6, U$34.C2
unnamed: SV34.4, U$34.B2
unnamed: SV34.2, U$34.A2
unnamed: SV34.35, U$34.V1
unnamed: SV34.33, U$34.U1
unnamed: SV34.31, U$34.T1
unnamed: SV34.29, U$34.S1
unnamed: SV34.27, U$34.R1
unnamed: SV34.25, U$34.P1
unnamed: SV34.23, U$34.N1
unnamed: SV34.21, U$34.M1
unnamed: SV34.19, U$34.L1
unnamed: SV34.17, U$34.K1
unnamed: SV34.15, U$34.J1
unnamed: SV34.13, U$34.H1
unnamed: SV34.11, U$34.F1
unnamed: SV34.9, U$34.E1
unnamed: SV34.7, U$34.D1
unnamed: SV34.5, U$34.C1
unnamed: SV34.3, U$34.B1
unnamed: SV34.1, U$34.A1
unnamed: SV35.36, U$35.V2
unnamed: SV35.34, U$35.U2
unnamed: SV35.32, U$35.T2
unnamed: SV35.30, U$35.S2
unnamed: SV35.28, U$35.R2
unnamed: SV35.26, U$35.P2
unnamed: SV35.24, U$35.N2
unnamed: SV35.22, U$35.M2
unnamed: SV35.20, U$35.L2
unnamed: SV35.18, U$35.K2
unnamed: SV35.16, U$35.J2
unnamed: SV35.14, U$35.H2
unnamed: SV35.12, U$35.F2
unnamed: SV35.10, U$35.E2
unnamed: SV35.8, U$35.D2
unnamed: SV35.6, U$35.C2
unnamed: SV35.4, U$35.B2
unnamed: SV35.2, U$35.A2
unnamed: SV35.35, U$35.V1
unnamed: SV35.33, U$35.U1
unnamed: SV35.31, U$35.T1
unnamed: SV35.29, U$35.S1
unnamed: SV35.27, U$35.R1
unnamed: SV35.25, U$35.P1
unnamed: SV35.23, U$35.N1
unnamed: SV35.21, U$35.M1
unnamed: SV35.19, U$35.L1
unnamed: SV35.17, U$35.K1
unnamed: SV35.15, U$35.J1
unnamed: SV35.13, U$35.H1
unnamed: SV35.11, U$35.F1
unnamed: SV35.9, U$35.E1
unnamed: SV35.7, U$35.D1
unnamed: SV35.5, U$35.C1
unnamed: SV35.3, U$35.B1
unnamed: SV35.1, U$35.A1
unnamed: SV36.36, U$36.V2
unnamed: SV36.34, U$36.U2
unnamed: SV36.32, U$36.T2
unnamed: SV36.30, U$36.S2
unnamed: SV36.28, U$36.R2
unnamed: SV36.26, U$36.P2
unnamed: SV36.24, U$36.N2
unnamed: SV36.22, U$36.M2
unnamed: SV36.20, U$36.L2
unnamed: SV36.18, U$36.K2
unnamed: SV36.16, U$36.J2
unnamed: SV36.14, U$36.H2
unnamed: SV36.12, U$36.F2
unnamed: SV36.10, U$36.E2
unnamed: SV36.8, U$36.D2
unnamed: SV36.6, U$36.C2
unnamed: SV36.4, U$36.B2
unnamed: SV36.2, U$36.A2
unnamed: SV36.35, U$36.V1
unnamed: SV36.33, U$36.U1
unnamed: SV36.31, U$36.T1
unnamed: SV36.29, U$36.S1
unnamed: SV36.27, U$36.R1
unnamed: SV36.25, U$36.P1
unnamed: SV36.23, U$36.N1
unnamed: SV36.21, U$36.M1
unnamed: SV36.19, U$36.L1
unnamed: SV36.17, U$36.K1
unnamed: SV36.15, U$36.J1
unnamed: SV36.13, U$36.H1
unnamed: SV36.11, U$36.F1
unnamed: SV36.9, U$36.E1
unnamed: SV36.7, U$36.D1
unnamed: SV36.5, U$36.C1
unnamed: SV36.3, U$36.B1
unnamed: SV36.1, U$36.A1
unnamed: SV37.36, U$37.V2
unnamed: SV37.34, U$37.U2
unnamed: SV37.32, U$37.T2
unnamed: SV37.30, U$37.S2
unnamed: SV37.28, U$37.R2
unnamed: SV37.26, U$37.P2
unnamed: SV37.24, U$37.N2
unnamed: SV37.22, U$37.M2
unnamed: SV37.20, U$37.L2
unnamed: SV37.18, U$37.K2
unnamed: SV37.16, U$37.J2
unnamed: SV37.14, U$37.H2
unnamed: SV37.12, U$37.F2
unnamed: SV37.10, U$37.E2
unnamed: SV37.8, U$37.D2
unnamed: SV37.6, U$37.C2
unnamed: SV37.4, U$37.B2
unnamed: SV37.2, U$37.A2
unnamed: SV37.35, U$37.V1
unnamed: SV37.33, U$37.U1
unnamed: SV37.31, U$37.T1
unnamed: SV37.29, U$37.S1
unnamed: SV37.27, U$37.R1
unnamed: SV37.25, U$37.P1
unnamed: SV37.23, U$37.N1
unnamed: SV37.21, U$37.M1
unnamed: SV37.19, U$37.L1
unnamed: SV37.17, U$37.K1
unnamed: SV37.15, U$37.J1
unnamed: SV37.13, U$37.H1
unnamed: SV37.11, U$37.F1
unnamed: SV37.9, U$37.E1
unnamed: SV37.7, U$37.D1
unnamed: SV37.5, U$37.C1
unnamed: SV37.3, U$37.B1
unnamed: SV37.1, U$37.A1
unnamed: SV38.36, U$38.V2
unnamed: SV38.34, U$38.U2
unnamed: SV38.32, U$38.T2
unnamed: SV38.30, U$38.S2
unnamed: SV38.28, U$38.R2
unnamed: SV38.26, U$38.P2
unnamed: SV38.24, U$38.N2
unnamed: SV38.22, U$38.M2
unnamed: SV38.20, U$38.L2
unnamed: SV38.18, U$38.K2
unnamed: SV38.16, U$38.J2
unnamed: SV38.14, U$38.H2
unnamed: SV38.12, U$38.F2
unnamed: SV38.10, U$38.E2
unnamed: SV38.8, U$38.D2
unnamed: SV38.6, U$38.C2
unnamed: SV38.4, U$38.B2
unnamed: SV38.2, U$38.A2
unnamed: SV38.35, U$38.V1
unnamed: SV38.33, U$38.U1
unnamed: SV38.31, U$38.T1
unnamed: SV38.29, U$38.S1
unnamed: SV38.27, U$38.R1
unnamed: SV38.25, U$38.P1
unnamed: SV38.23, U$38.N1
unnamed: SV38.21, U$38.M1
unnamed: SV38.19, U$38.L1
unnamed: SV38.17, U$38.K1
unnamed: SV38.15, U$38.J1
unnamed: SV38.13, U$38.H1
unnamed: SV38.11, U$38.F1
unnamed: SV38.9, U$38.E1
unnamed: SV38.7, U$38.D1
unnamed: SV38.5, U$38.C1
unnamed: SV38.3, U$38.B1
unnamed: SV38.1, U$38.A1
unnamed: SV39.36, U$39.V2
unnamed: SV39.34, U$39.U2
unnamed: SV39.32, U$39.T2
unnamed: SV39.30, U$39.S2
unnamed: SV39.28, U$39.R2
unnamed: SV39.26, U$39.P2
unnamed: SV39.24, U$39.N2
unnamed: SV39.22, U$39.M2
unnamed: SV39.20, U$39.L2
unnamed: SV39.18, U$39.K2
unnamed: SV39.16, U$39.J2
unnamed: SV39.14, U$39.H2
unnamed: SV39.12, U$39.F2
unnamed: SV39.10, U$39.E2
unnamed: SV39.8, U$39.D2
unnamed: SV39.6, U$39.C2
unnamed: SV39.4, U$39.B2
unnamed: SV39.2, U$39.A2
unnamed: SV39.35, U$39.V1
unnamed: SV39.33, U$39.U1
unnamed: SV39.31, U$39.T1
unnamed: SV39.29, U$39.S1
unnamed: SV39.27, U$39.R1
unnamed: SV39.25, U$39.P1
unnamed: SV39.23, U$39.N1
unnamed: SV39.21, U$39.M1
unnamed: SV39.19, U$39.L1
unnamed: SV39.17, U$39.K1
unnamed: SV39.15, U$39.J1
unnamed: SV39.13, U$39.H1
unnamed: SV39.11, U$39.F1
unnamed: SV39.9, U$39.E1
unnamed: SV39.7, U$39.D1
unnamed: SV39.5, U$39.C1
unnamed: SV39.3, U$39.B1
unnamed: SV39.1, U$39.A1
unnamed: SV40.36, U$40.V2
unnamed: SV40.34, U$40.U2
unnamed: SV40.32, U$40.T2
unnamed: SV40.30, U$40.S2
unnamed: SV40.28, U$40.R2
unnamed: SV40.26, U$40.P2
unnamed: SV40.24, U$40.N2
unnamed: SV40.22, U$40.M2
unnamed: SV40.20, U$40.L2
unnamed: SV40.18, U$40.K2
unnamed: SV40.16, U$40.J2
unnamed: SV40.14, U$40.H2
unnamed: SV40.12, U$40.F2
unnamed: SV40.10, U$40.E2
unnamed: SV40.8, U$40.D2
unnamed: SV40.6, U$40.C2
unnamed: SV40.4, U$40.B2
unnamed: SV40.2, U$40.A2
unnamed: SV40.35, U$40.V1
unnamed: SV40.33, U$40.U1
unnamed: SV40.31, U$40.T1
unnamed: SV40.29, U$40.S1
unnamed: SV40.27, U$40.R1
unnamed: SV40.25, U$40.P1
unnamed: SV40.23, U$40.N1
unnamed: SV40.21, U$40.M1
unnamed: SV40.19, U$40.L1
unnamed: SV40.17, U$40.K1
unnamed: SV40.15, U$40.J1
unnamed: SV40.13, U$40.H1
unnamed: SV40.11, U$40.F1
unnamed: SV40.9, U$40.E1
unnamed: SV40.7, U$40.D1
unnamed: SV40.5, U$40.C1
unnamed: SV40.3, U$40.B1
unnamed: SV40.1, U$40.A1
unnamed: SV41.36, U$41.V2
unnamed: SV41.34, U$41.U2
unnamed: SV41.32, U$41.T2
unnamed: SV41.30, U$41.S2
unnamed: SV41.28, U$41.R2
unnamed: SV41.26, U$41.P2
unnamed: SV41.24, U$41.N2
unnamed: SV41.22, U$41.M2
unnamed: SV41.20, U$41.L2
unnamed: SV41.18, U$41.K2
unnamed: SV41.16, U$41.J2
unnamed: SV41.14, U$41.H2
unnamed: SV41.12, U$41.F2
unnamed: SV41.10, U$41.E2
unnamed: SV41.8, U$41.D2
unnamed: SV41.6, U$41.C2
unnamed: SV41.4, U$41.B2
unnamed: SV41.2, U$41.A2
unnamed: SV41.35, U$41.V1
unnamed: SV41.33, U$41.U1
unnamed: SV41.31, U$41.T1
unnamed: SV41.29, U$41.S1
unnamed: SV41.27, U$41.R1
unnamed: SV41.25, U$41.P1
unnamed: SV41.23, U$41.N1
unnamed: SV41.21, U$41.M1
unnamed: SV41.19, U$41.L1
unnamed: SV41.17, U$41.K1
unnamed: SV41.15, U$41.J1
unnamed: SV41.13, U$41.H1
unnamed: SV41.11, U$41.F1
unnamed: SV41.9, U$41.E1
unnamed: SV41.7, U$41.D1
unnamed: SV41.5, U$41.C1
unnamed: SV41.3, U$41.B1
unnamed: SV41.1, U$41.A1
unnamed: SV42.36, U$42.V2
unnamed: SV42.34, U$42.U2
unnamed: SV42.32, U$42.T2
unnamed: SV42.30, U$42.S2
unnamed: SV42.28, U$42.R2
unnamed: SV42.26, U$42.P2
unnamed: SV42.24, U$42.N2
unnamed: SV42.22, U$42.M2
unnamed: SV42.20, U$42.L2
unnamed: SV42.18, U$42.K2
unnamed: SV42.16, U$42.J2
unnamed: SV42.14, U$42.H2
unnamed: SV42.12, U$42.F2
unnamed: SV42.10, U$42.E2
unnamed: SV42.8, U$42.D2
unnamed: SV42.6, U$42.C2
unnamed: SV42.4, U$42.B2
unnamed: SV42.2, U$42.A2
unnamed: SV42.35, U$42.V1
unnamed: SV42.33, U$42.U1
unnamed: SV42.31, U$42.T1
unnamed: SV42.29, U$42.S1
unnamed: SV42.27, U$42.R1
unnamed: SV42.25, U$42.P1
unnamed: SV42.23, U$42.N1
unnamed: SV42.21, U$42.M1
unnamed: SV42.19, U$42.L1
unnamed: SV42.17, U$42.K1
unnamed: SV42.15, U$42.J1
unnamed: SV42.13, U$42.H1
unnamed: SV42.11, U$42.F1
unnamed: SV42.9, U$42.E1
unnamed: SV42.7, U$42.D1
unnamed: SV42.5, U$42.C1
unnamed: SV42.3, U$42.B1
unnamed: SV42.1, U$42.A1
unnamed: SV43.36, U$43.V2
unnamed: SV43.34, U$43.U2
unnamed: SV43.32, U$43.T2
unnamed: SV43.30, U$43.S2
unnamed: SV43.28, U$43.R2
unnamed: SV43.26, U$43.P2
unnamed: SV43.24, U$43.N2
unnamed: SV43.22, U$43.M2
unnamed: SV43.20, U$43.L2
unnamed: SV43.18, U$43.K2
unnamed: SV43.16, U$43.J2
unnamed: SV43.14, U$43.H2
unnamed: SV43.12, U$43.F2
unnamed: SV43.10, U$43.E2
unnamed: SV43.8, U$43.D2
unnamed: SV43.6, U$43.C2
unnamed: SV43.4, U$43.B2
unnamed: SV43.2, U$43.A2
unnamed: SV43.35, U$43.V1
unnamed: SV43.33, U$43.U1
unnamed: SV43.31, U$43.T1
unnamed: SV43.29, U$43.S1
unnamed: SV43.27, U$43.R1
unnamed: SV43.25, U$43.P1
unnamed: SV43.23, U$43.N1
unnamed: SV43.21, U$43.M1
unnamed: SV43.19, U$43.L1
unnamed: SV43.17, U$43.K1
unnamed: SV43.15, U$43.J1
unnamed: SV43.13, U$43.H1
unnamed: SV43.11, U$43.F1
unnamed: SV43.9, U$43.E1
unnamed: SV43.7, U$43.D1
unnamed: SV43.5, U$43.C1
unnamed: SV43.3, U$43.B1
unnamed: SV43.1, U$43.A1
unnamed: SV44.36, U$44.V2
unnamed: SV44.34, U$44.U2
unnamed: SV44.32, U$44.T2
unnamed: SV44.30, U$44.S2
unnamed: SV44.28, U$44.R2
unnamed: SV44.26, U$44.P2
unnamed: SV44.24, U$44.N2
unnamed: SV44.22, U$44.M2
unnamed: SV44.20, U$44.L2
unnamed: SV44.18, U$44.K2
unnamed: SV44.16, U$44.J2
unnamed: SV44.14, U$44.H2
unnamed: SV44.12, U$44.F2
unnamed: SV44.10, U$44.E2
unnamed: SV44.8, U$44.D2
unnamed: SV44.6, U$44.C2
unnamed: SV44.4, U$44.B2
unnamed: SV44.2, U$44.A2
unnamed: SV44.35, U$44.V1
unnamed: SV44.33, U$44.U1
unnamed: SV44.31, U$44.T1
unnamed: SV44.29, U$44.S1
unnamed: SV44.27, U$44.R1
unnamed: SV44.25, U$44.P1
unnamed: SV44.23, U$44.N1
unnamed: SV44.21, U$44.M1
unnamed: SV44.19, U$44.L1
unnamed: SV44.17, U$44.K1
unnamed: SV44.15, U$44.J1
unnamed: SV44.13, U$44.H1
unnamed: SV44.11, U$44.F1
unnamed: SV44.9, U$44.E1
unnamed: SV44.7, U$44.D1
unnamed: SV44.5, U$44.C1
unnamed: SV44.3, U$44.B1
unnamed: SV44.1, U$44.A1
unnamed: SV45.36, U$45.V2
unnamed: SV45.34, U$45.U2
unnamed: SV45.32, U$45.T2
unnamed: SV45.30, U$45.S2
unnamed: SV45.28, U$45.R2
unnamed: SV45.26, U$45.P2
unnamed: SV45.24, U$45.N2
unnamed: SV45.22, U$45.M2
unnamed: SV45.20, U$45.L2
unnamed: SV45.18, U$45.K2
unnamed: SV45.16, U$45.J2
unnamed: SV45.14, U$45.H2
unnamed: SV45.12, U$45.F2
unnamed: SV45.10, U$45.E2
unnamed: SV45.8, U$45.D2
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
